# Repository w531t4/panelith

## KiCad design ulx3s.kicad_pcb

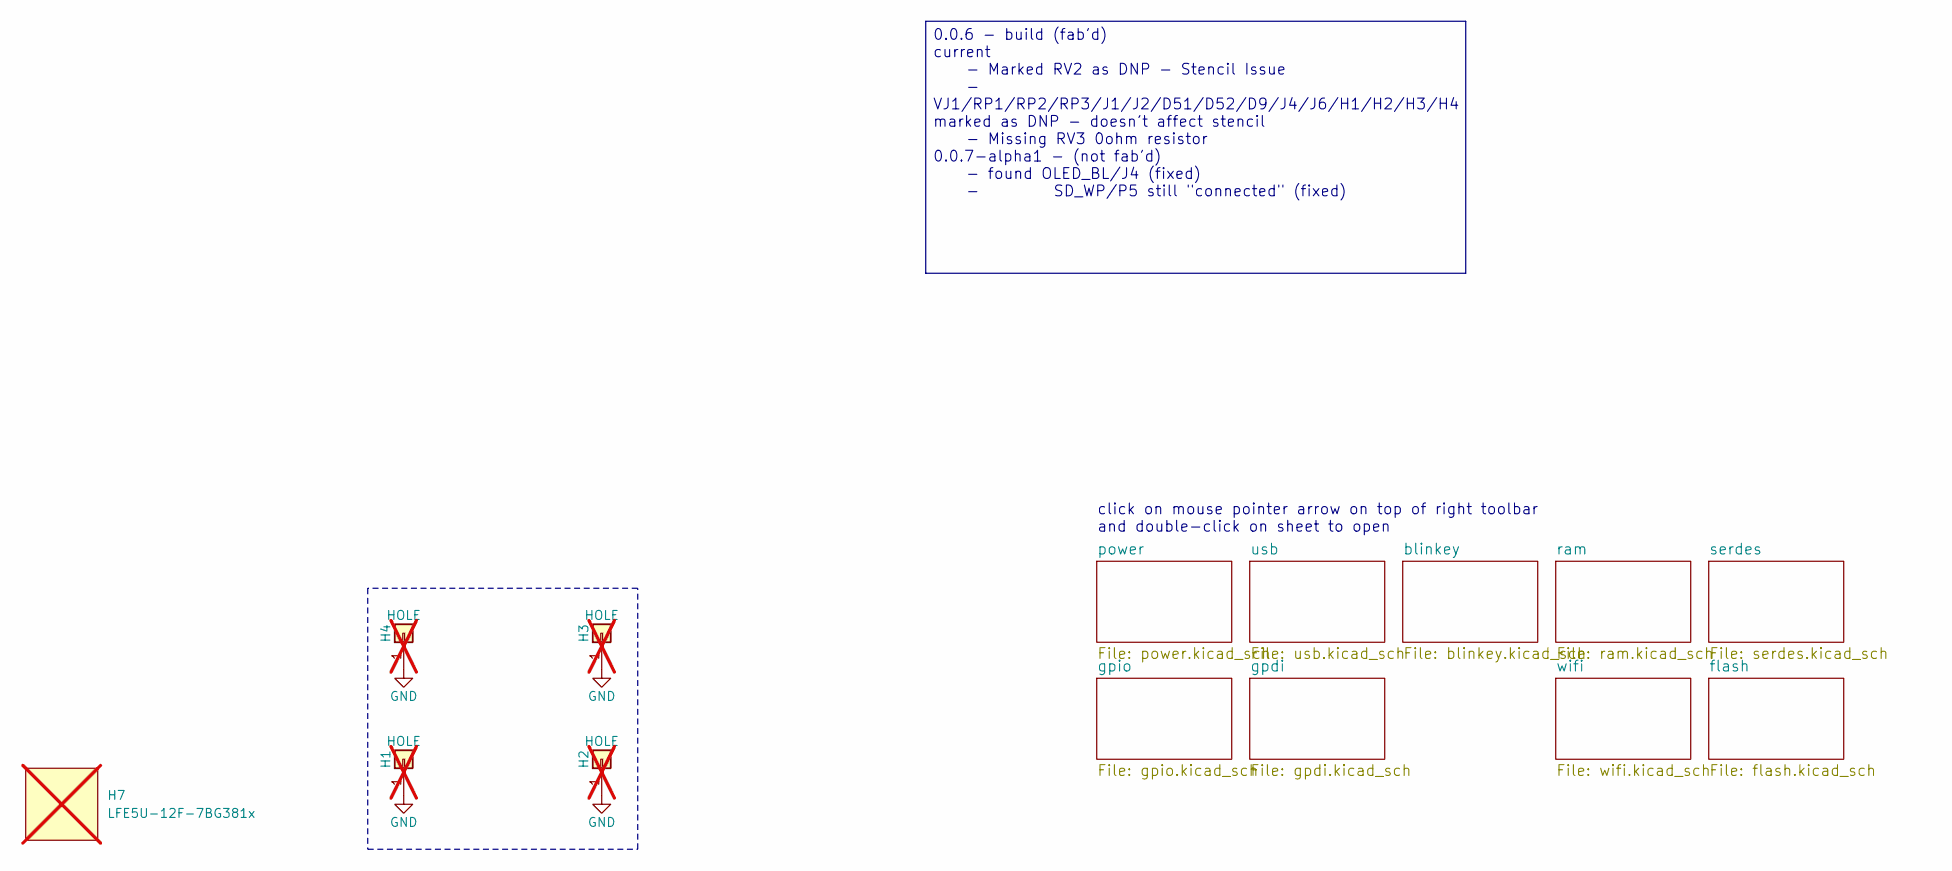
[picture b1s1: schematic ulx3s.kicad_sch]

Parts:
H1, H2, H3, H4: HOLE; MountingHole_3.2mm_M3_ISO14580_Pad; not fitted
H7: LFE5U-12F-7BG381x; Lattice_caBGA-381_17x17mm_Layout20x20_P0.8mm; MPN 842-LFE5U12F7BG381C; Digikey 220-2101-ND; not fitted

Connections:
unnamed: H1.1, H2.1, H3.1, H4.1

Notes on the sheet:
click on mouse pointer arrow on top of right toolbar and double-click on sheet to open
0.0.6 - build (fab'd) current - Marked RV2 as DNP - Stencil Issue - VJ1/RP1/RP2/RP3/J1/J2/D51/D52/D9/J4/J6/H1/H2/H3/H4 marked as DNP - doesn't affect stencil - Missing RV3 0ohm resistor 0.0.7-alpha1 - (not fab'd) - found OLED_BL/J4 (fixed) - SD_WP/P5 still "connected" (fixed)

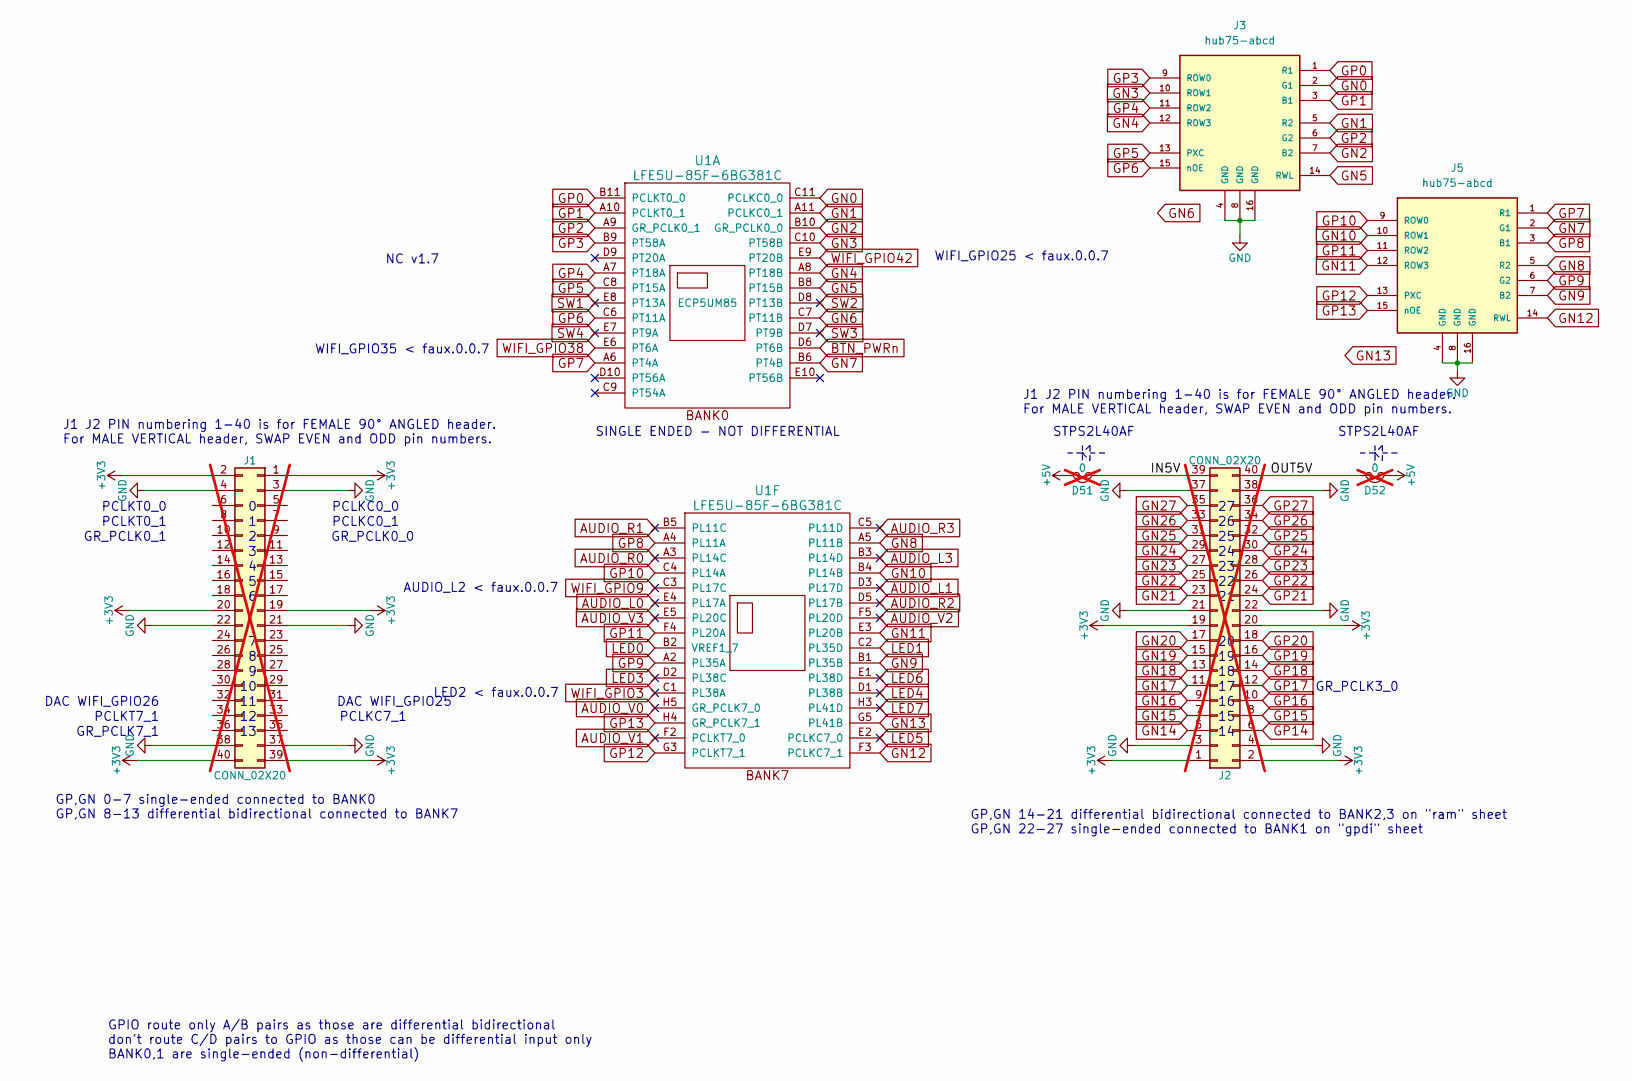
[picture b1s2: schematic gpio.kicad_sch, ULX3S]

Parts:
D51, D52: 0; D_SMA_Jumper_NC; not fitted
J1, J2: CONN_02X20; Socket_Strip_Angled_2x20; not fitted
J3, J5: hub75-abcd; SAMTEC-HTST-108-01-X-DV; MPN 200-HTST10801LDVP; Digikey SAM14030CT-ND
U1: LFE5U-85F-6BG381C; BGA-381_pitch0.8mm_dia0.4mm; MPN LFE5U-85F-6BG381C; LCSC C446029

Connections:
+5V: D51.1, D52.2; also elsewhere on the board
/gpio/IN5V: D51.2, J2.39
/gpio/OUT5V: D52.1, J2.40
AUDIO_L0: U1.E4 (PL17A)
AUDIO_L1: U1.D3 (PL17D)
AUDIO_L3: U1.B3 (PL14D)
AUDIO_R0: U1.A3 (PL14C)
AUDIO_R1: U1.B5 (PL11C)
AUDIO_R2: U1.D5 (PL17B)
AUDIO_R3: U1.C5 (PL11D)
AUDIO_V0: U1.H5 (GR_PCLK7_0)
AUDIO_V1: U1.F2 (PCLKT7_0)
AUDIO_V2: U1.F5 (PL20D)
AUDIO_V3: U1.E5 (PL20C)
BTN_PWRn: U1.D6 (PT6B); also elsewhere on the board
GN0: J3.2 (G1), U1.C11 (PCLKC0_0)
GN1: J3.5 (R2), U1.A11 (PCLKC0_1)
GN2: J3.7 (B2), U1.B10 (GR_PCLK0_0)
GN3: J3.10 (ROW1), U1.C10 (PT58B)
GN4: J3.12 (ROW3), U1.A8 (PT18B)
GN5: J3.14 (RWL), U1.B8 (PT15B)
GN6: U1.C7 (PT11B)
GN7: J5.2 (G1), U1.B6 (PT4B)
GN8: J5.5 (R2), U1.A5 (PL11B)
GN9: J5.7 (B2), U1.B1 (PL35B)
GN10: J5.10 (ROW1), U1.B4 (PL14B)
GN11: J5.12 (ROW3), U1.E3 (PL20B)
GN12: J5.14 (RWL), U1.F3 (PCLKC7_1); also elsewhere on the board
GN13: U1.G5 (PL41B); also elsewhere on the board
GND: J1.3, J1.4, J1.21, J1.22, J1.37, J1.38, J2.3, J2.4, J2.21, J2.22, J2.37, J2.38, J3.4 (GND), J3.8 (GND), J3.16 (GND), J5.4 (GND), J5.8 (GND), J5.16 (GND); also elsewhere on the board
GP0: J3.1 (R1), U1.B11 (PCLKT0_0)
GP1: J3.3 (B1), U1.A10 (PCLKT0_1)
GP2: J3.6 (G2), U1.A9 (GR_PCLK0_1)
GP3: J3.9 (ROW0), U1.B9 (PT58A)
GP4: J3.11 (ROW2), U1.A7 (PT18A)
GP5: J3.13 (PXC), U1.C8 (PT15A)
GP6: J3.15 (nOE), U1.C6 (PT11A)
GP7: J5.1 (R1), U1.A6 (PT4A)
GP8: J5.3 (B1), U1.A4 (PL11A)
GP9: J5.6 (G2), U1.A2 (PL35A)
GP10: J5.9 (ROW0), U1.C4 (PL14A)
GP11: J5.11 (ROW2), U1.F4 (PL20A)
GP12: J5.13 (PXC), U1.G3 (PCLKT7_1); also elsewhere on the board
GP13: J5.15 (nOE), U1.H4 (GR_PCLK7_1); also elsewhere on the board
LED0: U1.B2 (VREF1_7); also elsewhere on the board
LED1: U1.C2 (PL35D); also elsewhere on the board
LED3: U1.D2 (PL38C)
LED4: U1.D1 (PL38B)
LED5: U1.E2 (PCLKC7_0)
LED6: U1.E1 (PL38D)
LED7: U1.H3 (PL41D)
unnamed: J1.1, J1.2, J1.19, J1.20, J1.39, J1.40, J2.1, J2.2, J2.19, J2.20
SW1: U1.E8 (PT13A)
SW2: U1.D8 (PT13B)
SW3: U1.D7 (PT9B)
SW4: U1.E7 (PT9A)
WIFI_GPIO3: U1.C1 (PL38A); also elsewhere on the board
WIFI_GPIO9: U1.C3 (PL17C); also elsewhere on the board
WIFI_GPIO38: U1.E6 (PT6A); also elsewhere on the board
WIFI_GPIO42: U1.E9 (PT20B); also elsewhere on the board

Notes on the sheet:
GR_PCLK0_0
SINGLE ENDED - NOT DIFFERENTIAL
PCLKC0_1
LED2 < faux.0.0.7
J1 J2 PIN numbering 1-40 is for FEMALE 90° ANGLED header. For MALE VERTICAL header, SWAP EVEN and ODD pin numbers.
GPIO route only A/B pairs as those are differential bidirectional don't route C/D pairs to GPIO as those can be differential input only BANK0,1 are single-ended (non-differential)
WIFI_GPIO25 < faux.0.0.7
GP,GN 14-21 differential bidirectional connected to BANK2,3 on "ram" sheet GP,GN 22-27 single-ended connected to BANK1 on "gpdi" sheet
NC v1.7
AUDIO_L2 < faux.0.0.7
STPS2L40AF
DAC WIFI_GPIO26
GR_PCLK3_0
WIFI_GPIO35 < faux.0.0.7
PCLKT0_0
DAC WIFI_GPIO25
PCLKT7_1
PCLKT0_1
PCLKC7_1
GR_PCLK0_1
GR_PCLK7_1
PCLKC0_0
GP,GN 0-7 single-ended connected to BANK0 GP,GN 8-13 differential bidirectional connected to BANK7

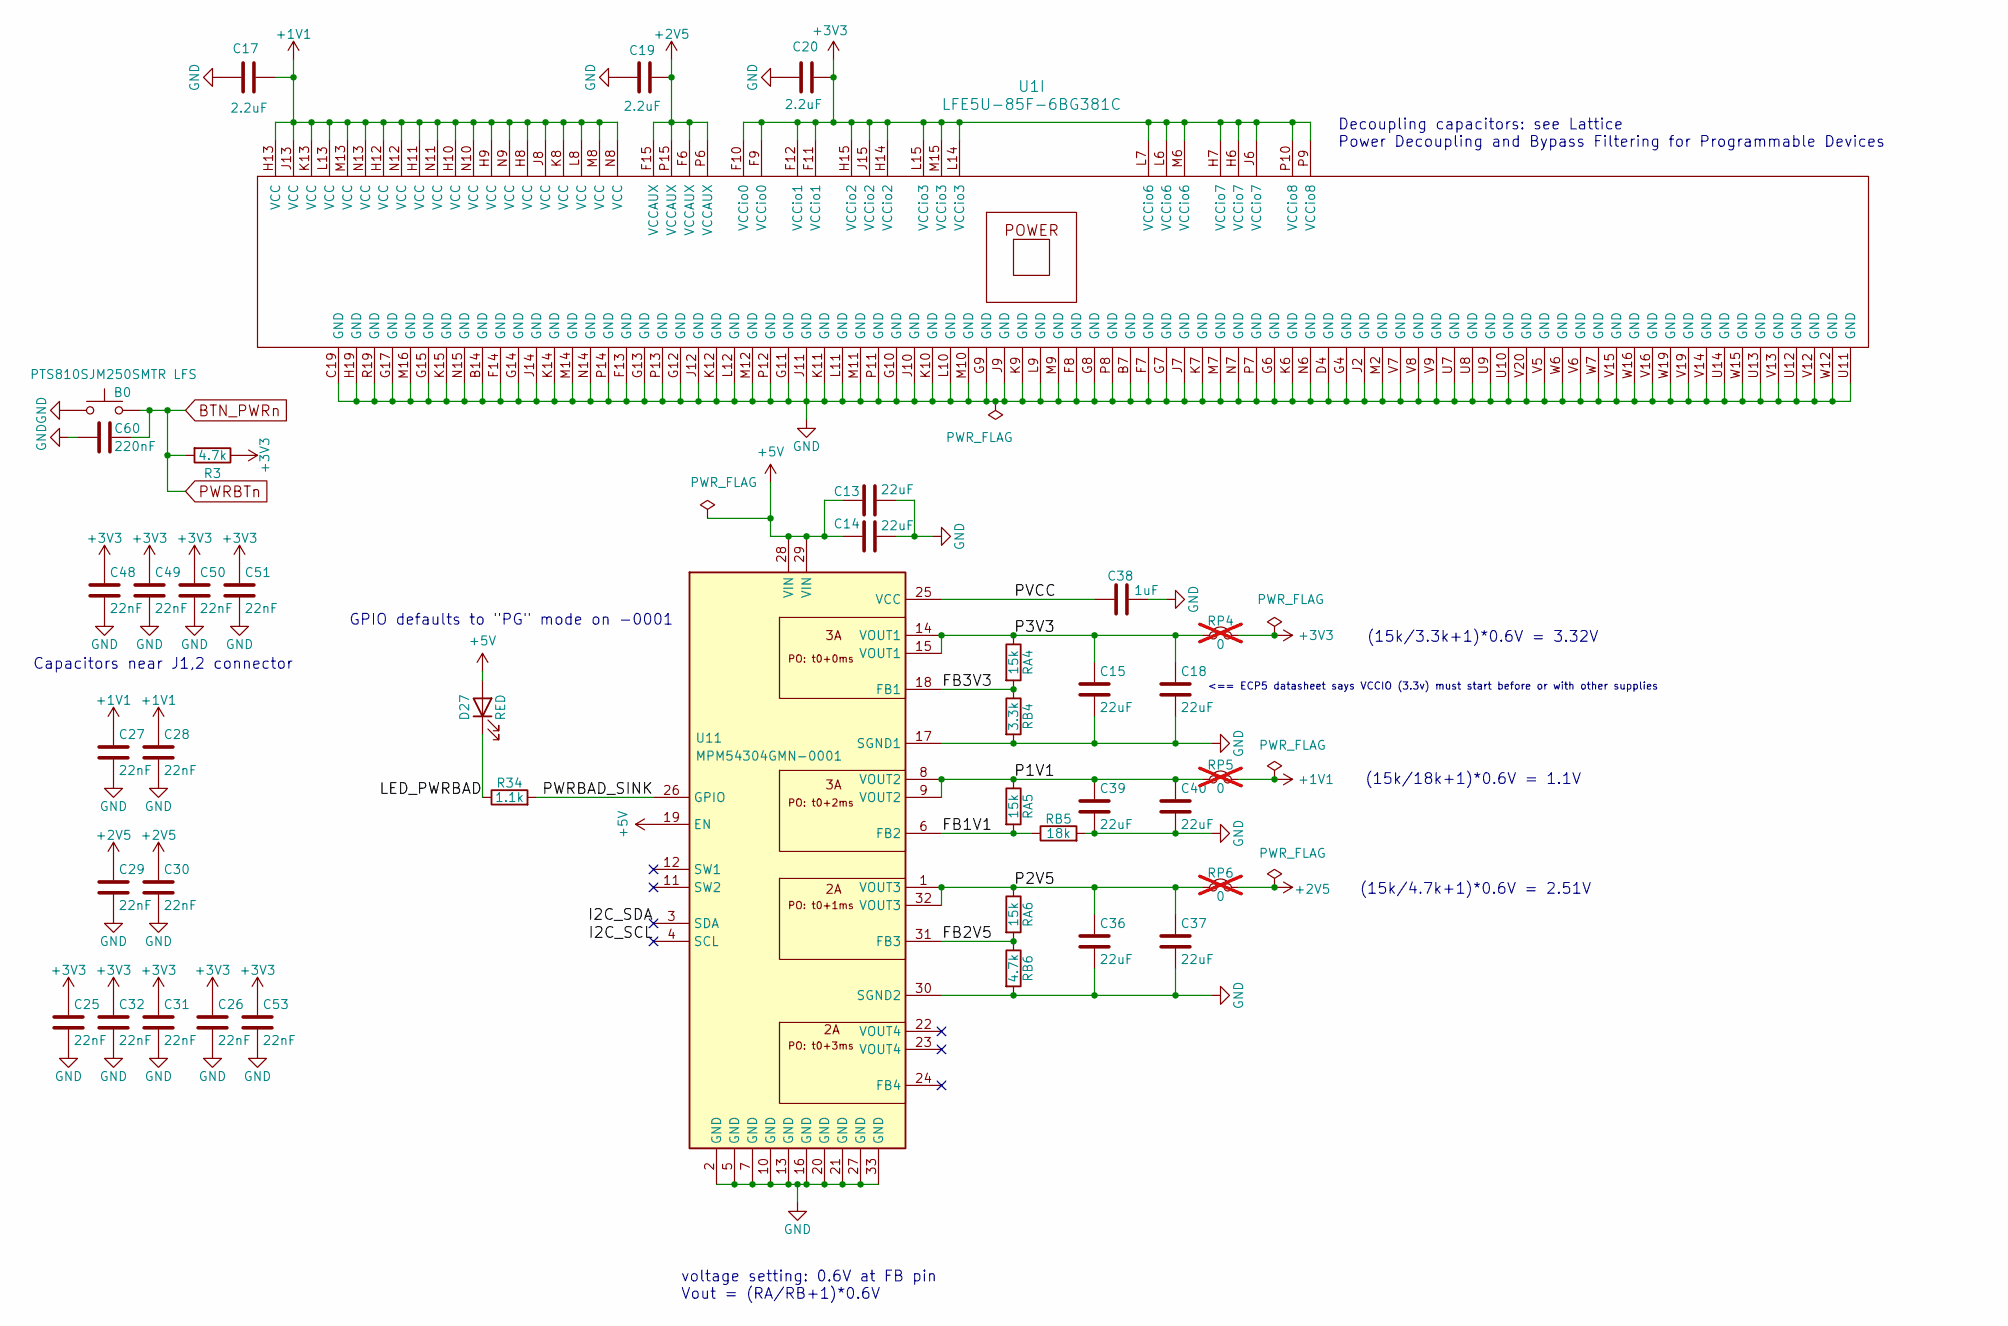
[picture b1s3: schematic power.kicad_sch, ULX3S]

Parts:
B0: PTS810SJM250SMTR LFS; PTS810_CNK; MPN 611-PTS810SJM250SMTR; Digikey CKN10502CT-ND
C13, C14: 22uF; C_0805_2012Metric; MPN 603-CC805MKX5R6BB226; Mouser 81-GRM21BR61A226ME1L
C15, C18, C36, C37, C39, C40: 22uF; C_0805_2012Metric; MPN 603-CC805MKX5R6BB226; Digikey 311-1900-1-ND
C17, C19, C20: 2.2uF; C_0805_2012Metric; MPN CC0805MRX5R6BB225; LCSC C87995
C25: 22nF; C_0603_1608Metric; MPN CC0603JRX7R8BB223; Mouser 603-CC603KRX7R7BB223
C26, C27, C28, C29, C30, C31, C32, C48, C49, C50, C51, C53: 22nF; C_0603_1608Metric; MPN CC0603JRX7R8BB223; LCSC C107137
C38: 1uF; C_0805_2012Metric; MPN 603-CC805KRX5R6BB105; Digikey 311-3423-1-ND
C60: 220nF; C_0603_1608Metric; MPN CC0603KRX7R8BB224; LCSC C326805
D27: RED; LED_0805_2012Metric; MPN LTST-C170KRKT; Mouser_URL www.mouser.com
R3: 4.7k; R_0603_1608Metric; MPN 603-RC0603FR-074K7L; LCSC C218056
R34: 1.1k; R_0603_1608Metric; MPN 13-AC0603FR-071K1LCT-ND; Digikey 13-AC0603FR-071K1LCT-ND
RA4, RA5, RA6: 15k; R_0603_1608Metric; MPN RC0603FR-0715KL; LCSC C217750
RB4: 3.3k; R_0603_1608Metric; MPN RT0603FRE073K3L; Mouser 603-RC0603FR-073K3L
RB5: 18k; R_0603_1608Metric; MPN RC0603FR-1018KL; Mouser 71-CRCW060318K0FKEAC
RB6: 4.7k; R_0603_1608Metric; MPN 603-RC0603FR-074K7L; LCSC C218056
RP4, RP5, RP6: 0; R_0805_2012Metric_Pad1.20x1.40mm_HandSolder; MPN 603-RC0805JR-070RL; Mouser_URL www.mouser.com; not fitted
U1: LFE5U-85F-6BG381C; BGA-381_pitch0.8mm_dia0.4mm; MPN LFE5U-85F-6BG381C; LCSC C446029
U11: MPM54304GMN-0001; MPM54304GMN0001; Manufacturer_Part_Number MPM54304GMN-0001; Mouser Part Number 946-MPM54304GMN-0001

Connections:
+1V1: C17.2, C27.1, C28.1, RP5.2, U1.H8 (VCC), U1.H9 (VCC), U1.H10 (VCC), U1.H11 (VCC), U1.H12 (VCC), U1.H13 (VCC), U1.J8 (VCC), U1.J13 (VCC), U1.K8 (VCC), U1.K13 (VCC), U1.L8 (VCC), U1.L13 (VCC), U1.M8 (VCC), U1.M13 (VCC), U1.N8 (VCC), U1.N9 (VCC), U1.N10 (VCC), U1.N11 (VCC), U1.N12 (VCC), U1.N13 (VCC)
+2V5: C19.1, C29.1, C30.1, RP6.2, U1.F6 (VCCAUX), U1.F15 (VCCAUX), U1.P6 (VCCAUX), U1.P15 (VCCAUX)
+3V3: C20.2, C25.1, C26.1, C31.1, C32.1, C48.1, C49.1, C50.1, C51.1, C53.1, R3.1, RP4.2, U1.F9 (VCCio0), U1.F10 (VCCio0), U1.F11 (VCCio1), U1.F12 (VCCio1), U1.H6 (VCCio7), U1.H7 (VCCio7), U1.H14 (VCCio2), U1.H15 (VCCio2), U1.J6 (VCCio7), U1.J15 (VCCio2), U1.L6 (VCCio6), U1.L7 (VCCio6), U1.L14 (VCCio3), U1.L15 (VCCio3), U1.M6 (VCCio6), U1.M15 (VCCio3), U1.P9 (VCCio8), U1.P10 (VCCio8); also elsewhere on the board
+5V: C13.1, C14.1, D27.2 (A), U11.19 (EN), U11.28 (VIN), U11.29 (VIN); also elsewhere on the board
/power/FB1V1: RA5.2, RB5.1, U11.6 (FB2)
/power/FB2V5: RA6.2, RB6.1, U11.31 (FB3)
/power/FB3V3: RA4.2, RB4.1, U11.18 (FB1)
/power/I2C_SCL: U11.4 (SCL)
/power/I2C_SDA: U11.3 (SDA)
/power/LED_PWRBAD: D27.1 (K), R34.1
/power/P1V1: C39.1, C40.1, RA5.1, RP5.1, U11.8 (VOUT2), U11.9 (VOUT2)
/power/P2V5: C36.1, C37.1, RA6.1, RP6.1, U11.1 (VOUT3), U11.32 (VOUT3)
/power/P3V3: C15.1, C18.1, RA4.1, RP4.1, U11.14 (VOUT1), U11.15 (VOUT1)
/power/PVCC: C38.1, U11.25 (VCC)
/power/PWRBAD_SINK: R34.2, U11.26 (GPIO)
BTN_PWRn: B0.1, C60.1, R3.2; also elsewhere on the board
GND: B0.2, C13.2, C14.2, C15.2, C17.1, C18.2, C19.2, C20.1, C25.2, C26.2, C27.2, C28.2, C29.2, C30.2, C31.2, C32.2, C36.2, C37.2, C38.2, C39.2, C40.2, C48.2, C49.2, C50.2, C51.2, C53.2, C60.2, RB4.2, RB5.2, RB6.2, U1.B7 (GND), U1.B14 (GND), U1.C19 (GND), U1.D4 (GND), U1.F7 (GND), U1.F8 (GND), U1.F13 (GND), U1.F14 (GND), U1.G4 (GND), U1.G6 (GND), U1.G7 (GND), U1.G8 (GND), U1.G9 (GND), U1.G10 (GND), U1.G11 (GND), U1.G12 (GND), U1.G13 (GND), U1.G14 (GND), U1.G15 (GND), U1.G17 (GND), U1.H19 (GND), U1.J2 (GND), U1.J7 (GND), U1.J9 (GND), U1.J10 (GND), U1.J11 (GND), U1.J12 (GND), U1.J14 (GND), U1.K6 (GND), U1.K7 (GND), U1.K9 (GND), U1.K10 (GND), U1.K11 (GND), U1.K12 (GND), U1.K14 (GND), U1.K15 (GND), U1.L9 (GND), U1.L10 (GND), U1.L11 (GND), U1.L12 (GND), U1.M2 (GND), U1.M7 (GND), U1.M9 (GND), U1.M10 (GND), U1.M11 (GND), U1.M12 (GND), U1.M14 (GND), U1.M16 (GND), U1.N6 (GND), U1.N7 (GND), U1.N14 (GND), U1.N15 (GND), U1.P7 (GND), U1.P8 (GND), U1.P11 (GND), U1.P12 (GND), U1.P13 (GND), U1.P14 (GND), U1.R19 (GND), U1.U7 (GND), U1.U8 (GND), U1.U9 (GND), U1.U10 (GND), U1.U11 (GND), U1.U12 (GND), U1.U13 (GND), U1.U14 (GND), U1.V5 (GND), U1.V6 (GND), U1.V7 (GND), U1.V8 (GND), U1.V9 (GND), U1.V12 (GND), U1.V13 (GND), U1.V14 (GND), U1.V15 (GND), U1.V16 (GND), U1.V19 (GND), U1.V20 (GND), U1.W6 (GND), U1.W7 (GND), U1.W12 (GND), U1.W15 (GND), U1.W16 (GND), U1.W19 (GND), U11.2 (GND), U11.5 (GND), U11.7 (GND), U11.10 (GND), U11.13 (GND), U11.16 (GND), U11.17 (SGND1), U11.20 (GND), U11.21 (GND), U11.27 (GND), U11.30 (SGND2), U11.33 (GND); also elsewhere on the board

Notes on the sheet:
GPIO defaults to "PG" mode on -0001
(15k/4.7k+1)*0.6V = 2.51V
<== ECP5 datasheet says VCCIO (3.3v) must start before or with other supplies
(15k/18k+1)*0.6V = 1.1V
Decoupling capacitors: see Lattice Power Decoupling and Bypass Filtering for Programmable Devices
(15k/3.3k+1)*0.6V = 3.32V
Capacitors near J1,2 connector
voltage setting: 0.6V at FB pin Vout = (RA/RB+1)*0.6V

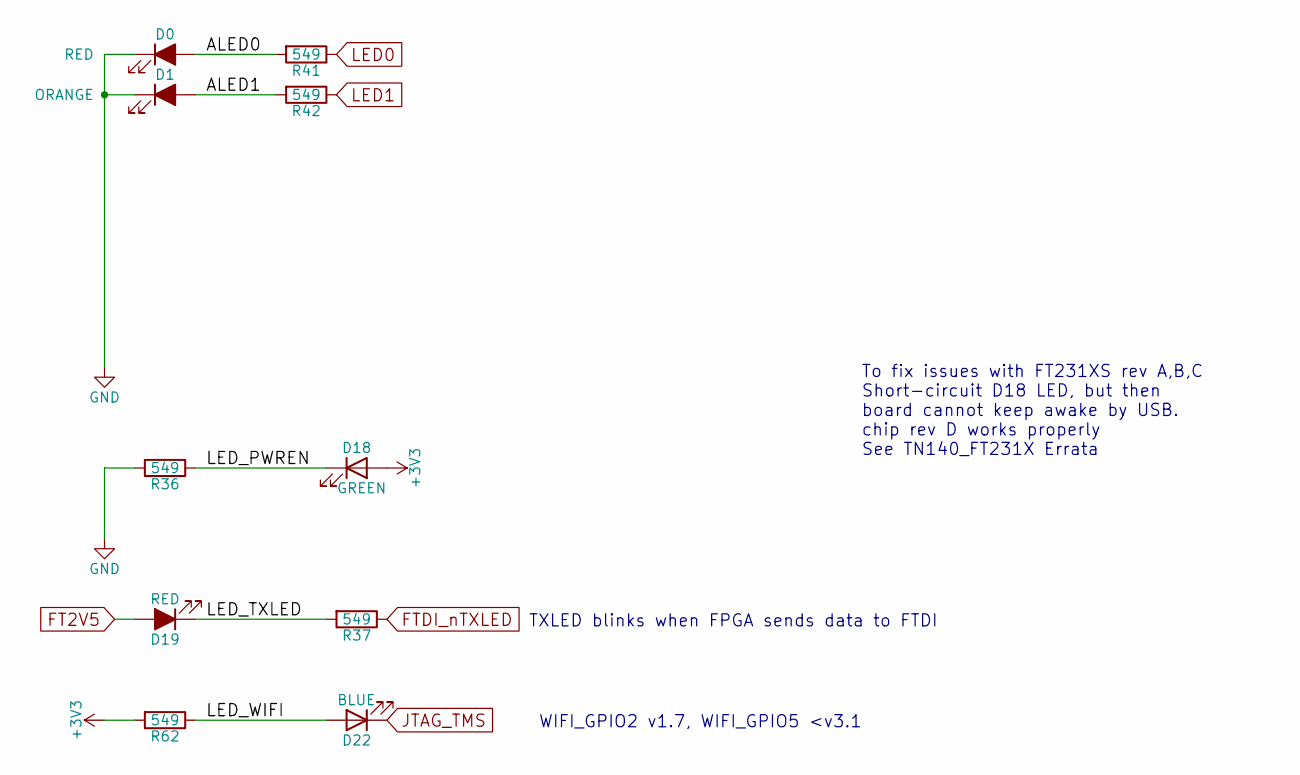
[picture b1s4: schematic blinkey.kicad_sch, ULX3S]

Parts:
D0: RED; LED_0805_2012Metric; MPN LTST-C170KRKT; Mouser 859-LTST-C170KRKT
D1: ORANGE; LED_0805_2012Metric; MPN LTST-C170KFKT; Mouser 859-LTST-C170KFKT
D18: GREEN; LED_0805_2012Metric; MPN LTST-C170TGKT; Mouser 859-LTST-C170TGKT
D19: RED; LED_0805_2012Metric; MPN LTST-C170KRKT; Mouser_URL www.mouser.com
D22: BLUE; LED_0805_2012Metric; MPN LTST-C170TBKT; Mouser 859-LTST-C170TBKT
R36, R37, R41, R42, R62: 549; R_0603_1608Metric; MPN 13-AC0603FR-07549RLCT-ND; Digikey 13-AC0603FR-07549RLCT-ND

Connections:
+3V3: D18.2 (A), R62.2; also elsewhere on the board
/blinkey/ALED0: D0.2 (A), R41.2
/blinkey/ALED1: D1.2 (A), R42.2
/blinkey/LED_PWREN: D18.1 (K), R36.1
/blinkey/LED_TXLED: D19.1 (K), R37.2
/blinkey/LED_WIFI: D22.2 (A), R62.1
FT2V5: D19.2 (A); also elsewhere on the board
FTDI_nTXLED: R37.1; also elsewhere on the board
GND: D0.1 (K), D1.1 (K), R36.2; also elsewhere on the board
JTAG_TMS: D22.1 (K); also elsewhere on the board
LED0: R41.1; also elsewhere on the board
LED1: R42.1; also elsewhere on the board

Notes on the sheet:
To fix issues with FT231XS rev A,B,C Short-circuit D18 LED, but then board cannot keep awake by USB. chip rev D works properly See TN140_FT231X Errata
TXLED blinks when FPGA sends data to FTDI
WIFI_GPIO2 v1.7, WIFI_GPIO5 <v3.1

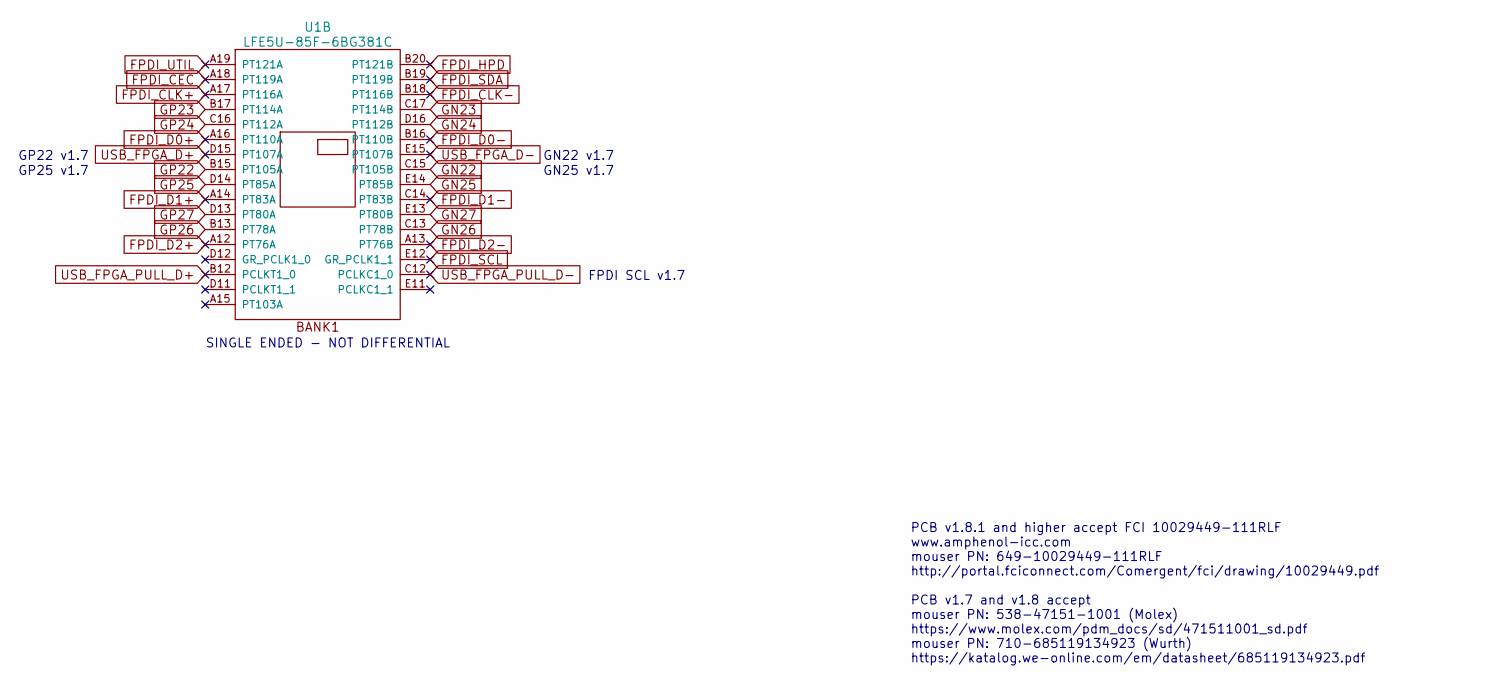
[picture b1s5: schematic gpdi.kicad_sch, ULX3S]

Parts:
U1: LFE5U-85F-6BG381C; BGA-381_pitch0.8mm_dia0.4mm; MPN LFE5U-85F-6BG381C; Mouser_URL www.mouser.com

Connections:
FPDI_CEC: U1.A18 (PT119A)
FPDI_CLK+: U1.A17 (PT116A)
FPDI_CLK-: U1.B18 (PT116B)
FPDI_D0+: U1.A16 (PT110A)
FPDI_D0-: U1.B16 (PT110B)
FPDI_D1+: U1.A14 (PT83A)
FPDI_D1-: U1.C14 (PT83B)
FPDI_D2+: U1.A12 (PT76A)
FPDI_D2-: U1.A13 (PT76B)
FPDI_HPD: U1.B20 (PT121B)
FPDI_SCL: U1.E12 (GR_PCLK1_1)
FPDI_SDA: U1.B19 (PT119B)
FPDI_UTIL: U1.A19 (PT121A)
GN22: U1.C15 (PT105B)
GN23: U1.C17 (PT114B)
GN24: U1.D16 (PT112B)
GN25: U1.E14 (PT85B)
GN26: U1.C13 (PT78B)
GN27: U1.E13 (PT80B)
GP22: U1.B15 (PT105A)
GP23: U1.B17 (PT114A)
GP24: U1.C16 (PT112A)
GP25: U1.D14 (PT85A)
GP26: U1.B13 (PT78A)
GP27: U1.D13 (PT80A)
USB_FPGA_D+: U1.D15 (PT107A); also elsewhere on the board
USB_FPGA_D-: U1.E15 (PT107B); also elsewhere on the board
USB_FPGA_PULL_D+: U1.B12 (PCLKT1_0)
USB_FPGA_PULL_D-: U1.C12 (PCLKC1_0)

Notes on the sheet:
PCB v1.8.1 and higher accept FCI 10029449-111RLF www.amphenol-icc.com mouser PN: 649-10029449-111RLF http://portal.fciconnect.com/Comergent/fci/drawing/10029449.pdf PCB v1.7 and v1.8 accept mouser PN: 538-47151-1001 (Molex) https://www.molex.com/pdm_docs/sd/471511001_sd.pdf mouser PN: 710-685119134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
GN22 v1.7
GN25 v1.7
GP25 v1.7
FPDI SCL v1.7
SINGLE ENDED - NOT DIFFERENTIAL
GP22 v1.7

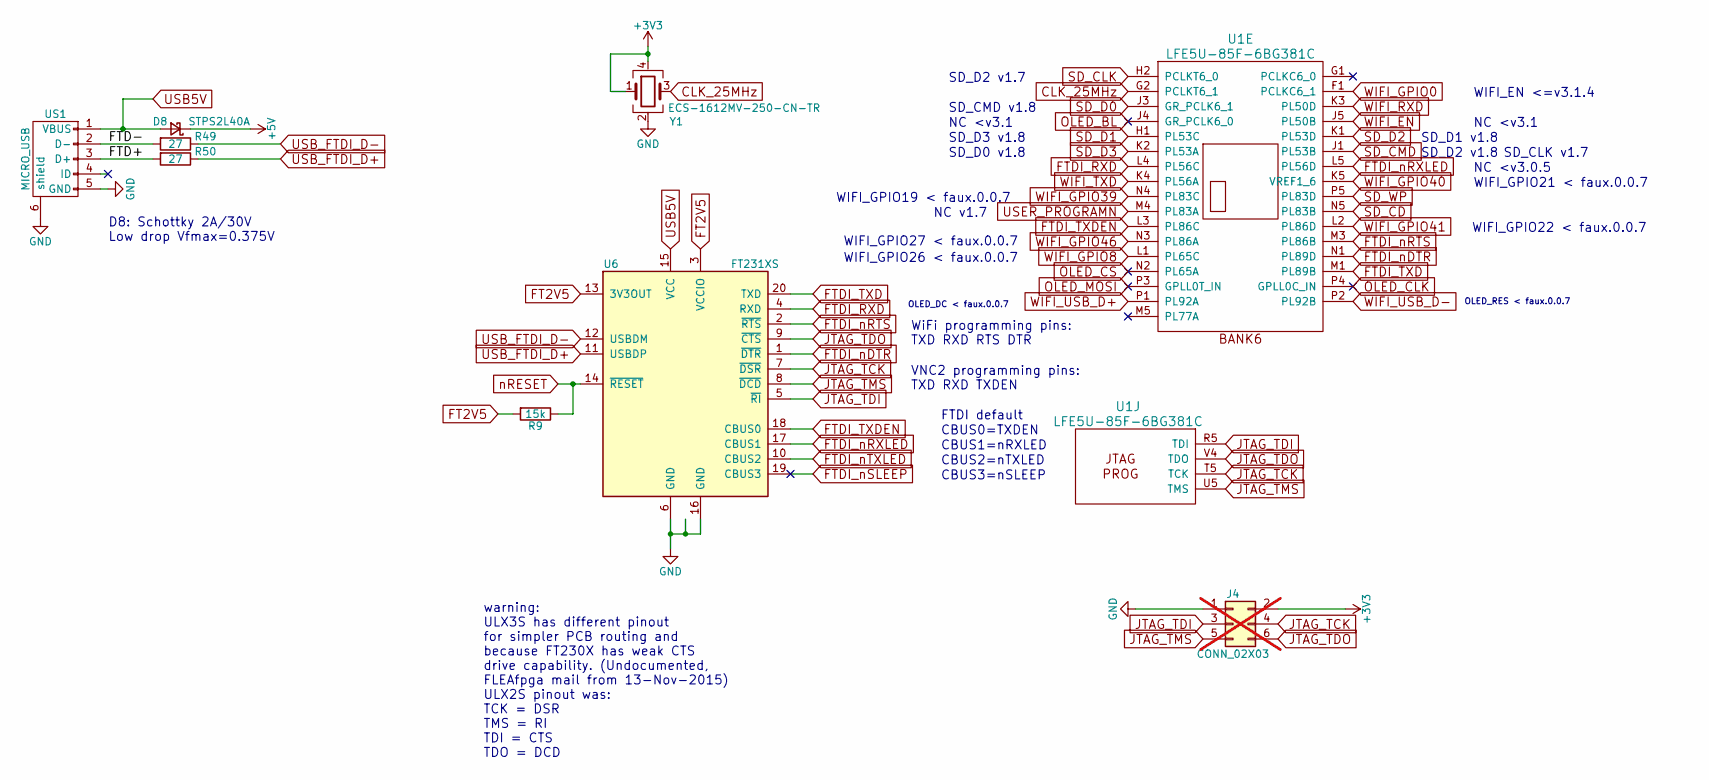
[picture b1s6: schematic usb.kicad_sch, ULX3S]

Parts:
D8: STPS2L40A; D_SMA; MPN 511-STPS2L30A; Mouser 511-STPS2L40AF
J4: CONN_02X03; PinSocket_2x03_P2.54mm_Vertical; not fitted
R9: 15k; R_0603_1608Metric; MPN RC0603FR-0715KL; Mouser 603-AC0603FR-1015KL
R49: 27; R_0603_1608Metric; MPN AC0603JR-0727RL; Mouser 603-AC0603JR-0727RL
R50: 27; R_0603_1608Metric; MPN AC0603JR-0727RL; LCSC C325726
U1: LFE5U-85F-6BG381C; BGA-381_pitch0.8mm_dia0.4mm; MPN LFE5U-85F-6BG381C; LCSC C446029
U6: FT231XS; FT231X-SSOP-20_4.4x6.5mm_Pitch0.65mm; MPN 895-FT231XS-U; Mouser 895-FT231XQ-R
US1: MICRO_USB; USB-MICRO-B-FCI-10118192-0001LF; MPN 10118192-0001LF; Mouser 649-10118192-0001LF
Y1: ECS-1612MV-250-CN-TR; OSC_ECS-1612MV-250-CN-TR-4; MPN 520-1612MV-250-CNT; Digikey XC2830CT-ND

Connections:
+3V3: J4.2, Y1.1, Y1.4 (VDD); also elsewhere on the board
+5V: D8.1 (K); also elsewhere on the board
/usb/FTD+: R50.2, US1.3 (D+)
/usb/FTD-: R49.2, US1.2 (D-)
CLK_25MHz: U1.G2 (PCLKT6_1), Y1.3
FT2V5: R9.2, U6.3 (VCCIO), U6.13 (3V3OUT); also elsewhere on the board
FTDI_RXD: U1.L4 (PL56C), U6.4 (RXD)
FTDI_TXD: U1.M1 (PL89B), U6.20 (TXD)
FTDI_TXDEN: U1.L3 (PL86C), U6.18 (CBUS0)
FTDI_nDTR: U1.N1 (PL89D), U6.1 (~DTR)
FTDI_nRTS: U1.M3 (PL86B), U6.2 (~RTS)
FTDI_nRXLED: U1.L5 (PL56D), U6.17 (CBUS1)
FTDI_nSLEEP: U6.19 (CBUS3)
FTDI_nTXLED: U6.10 (CBUS2); also elsewhere on the board
GND: J4.1, U6.6 (GND), U6.16 (GND), US1.5 (GND), US1.6 (shield), Y1.2 (GND); also elsewhere on the board
JTAG_TCK: J4.4, U1.T5 (TCK), U6.7 (~DSR); also elsewhere on the board
JTAG_TDI: J4.3, U1.R5 (TDI), U6.5 (~RI); also elsewhere on the board
JTAG_TDO: J4.6, U1.V4 (TDO), U6.9 (~CTS); also elsewhere on the board
JTAG_TMS: J4.5, U1.U5 (TMS), U6.8 (~DCD); also elsewhere on the board
OLED_BL: U1.J4 (GR_PCLK6_0)
OLED_CLK: U1.P4 (GPLL0C_IN)
OLED_CS: U1.N2 (PL65A)
OLED_MOSI: U1.P3 (GPLL0T_IN)
SD_CD: U1.N5 (PL83B)
SD_CLK: U1.H2 (PCLKT6_0); also elsewhere on the board
SD_CMD: U1.J1 (PL53B); also elsewhere on the board
SD_D0: U1.J3 (GR_PCLK6_1); also elsewhere on the board
SD_D1: U1.H1 (PL53C); also elsewhere on the board
SD_D2: U1.K1 (PL53D); also elsewhere on the board
SD_D3: U1.K2 (PL53A); also elsewhere on the board
SD_WP: U1.P5 (PL83D)
USB5V: D8.2 (A), U6.15 (VCC), US1.1 (VBUS)
USB_FTDI_D+: R50.1, U6.11 (USBDP)
USB_FTDI_D-: R49.1, U6.12 (USBDM)
USER_PROGRAMN: U1.M4 (PL83A); also elsewhere on the board
WIFI_EN: U1.J5 (PL50B); also elsewhere on the board
WIFI_GPIO0: U1.F1 (PCLKC6_1); also elsewhere on the board
WIFI_GPIO8: U1.L1 (PL65C); also elsewhere on the board
WIFI_GPIO39: U1.N4 (PL83C); also elsewhere on the board
WIFI_GPIO40: U1.K5 (VREF1_6); also elsewhere on the board
WIFI_GPIO41: U1.L2 (PL86D); also elsewhere on the board
WIFI_GPIO46: U1.N3 (PL86A); also elsewhere on the board
WIFI_RXD: U1.K3 (PL50D); also elsewhere on the board
WIFI_TXD: U1.K4 (PL56A); also elsewhere on the board
WIFI_USB_D+: U1.P1 (PL92A); also elsewhere on the board
WIFI_USB_D-: U1.P2 (PL92B); also elsewhere on the board
nRESET: R9.1, U6.14 (~RESET)

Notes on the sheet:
WIFI_EN <=v3.1.4
CBUS3=nSLEEP
SD_CLK v1.7
OLED_DC < faux.0.0.7
SD_D0 v1.8
CBUS1=nRXLED
WIFI_GPIO22 < faux.0.0.7
SD_D2 v1.7
NC <v3.1
FTDI default
WIFI_GPIO27 < faux.0.0.7
SD_CMD v1.8
warning: ULX3S has different pinout for simpler PCB routing and because FT230X has weak CTS drive capability. (Undocumented, FLEAfpga mail from 13-Nov-2015) ULX2S pinout was: TCK = DSR TMS = RI TDI = CTS TDO = DCD
OLED_RES < faux.0.0.7
CBUS2=nTXLED
CBUS0=TXDEN
NC v1.7
WiFi programming pins: TXD RXD RTS DTR
NC <v3.0.5
VNC2 programming pins: TXD RXD TXDEN
WIFI_GPIO19 < faux.0.0.7
WIFI_GPIO21 < faux.0.0.7
WIFI_GPIO26 < faux.0.0.7
D8: Schottky 2A/30V Low drop Vfmax=0.375V
SD_D1 v1.8
SD_D3 v1.8
SD_D2 v1.8

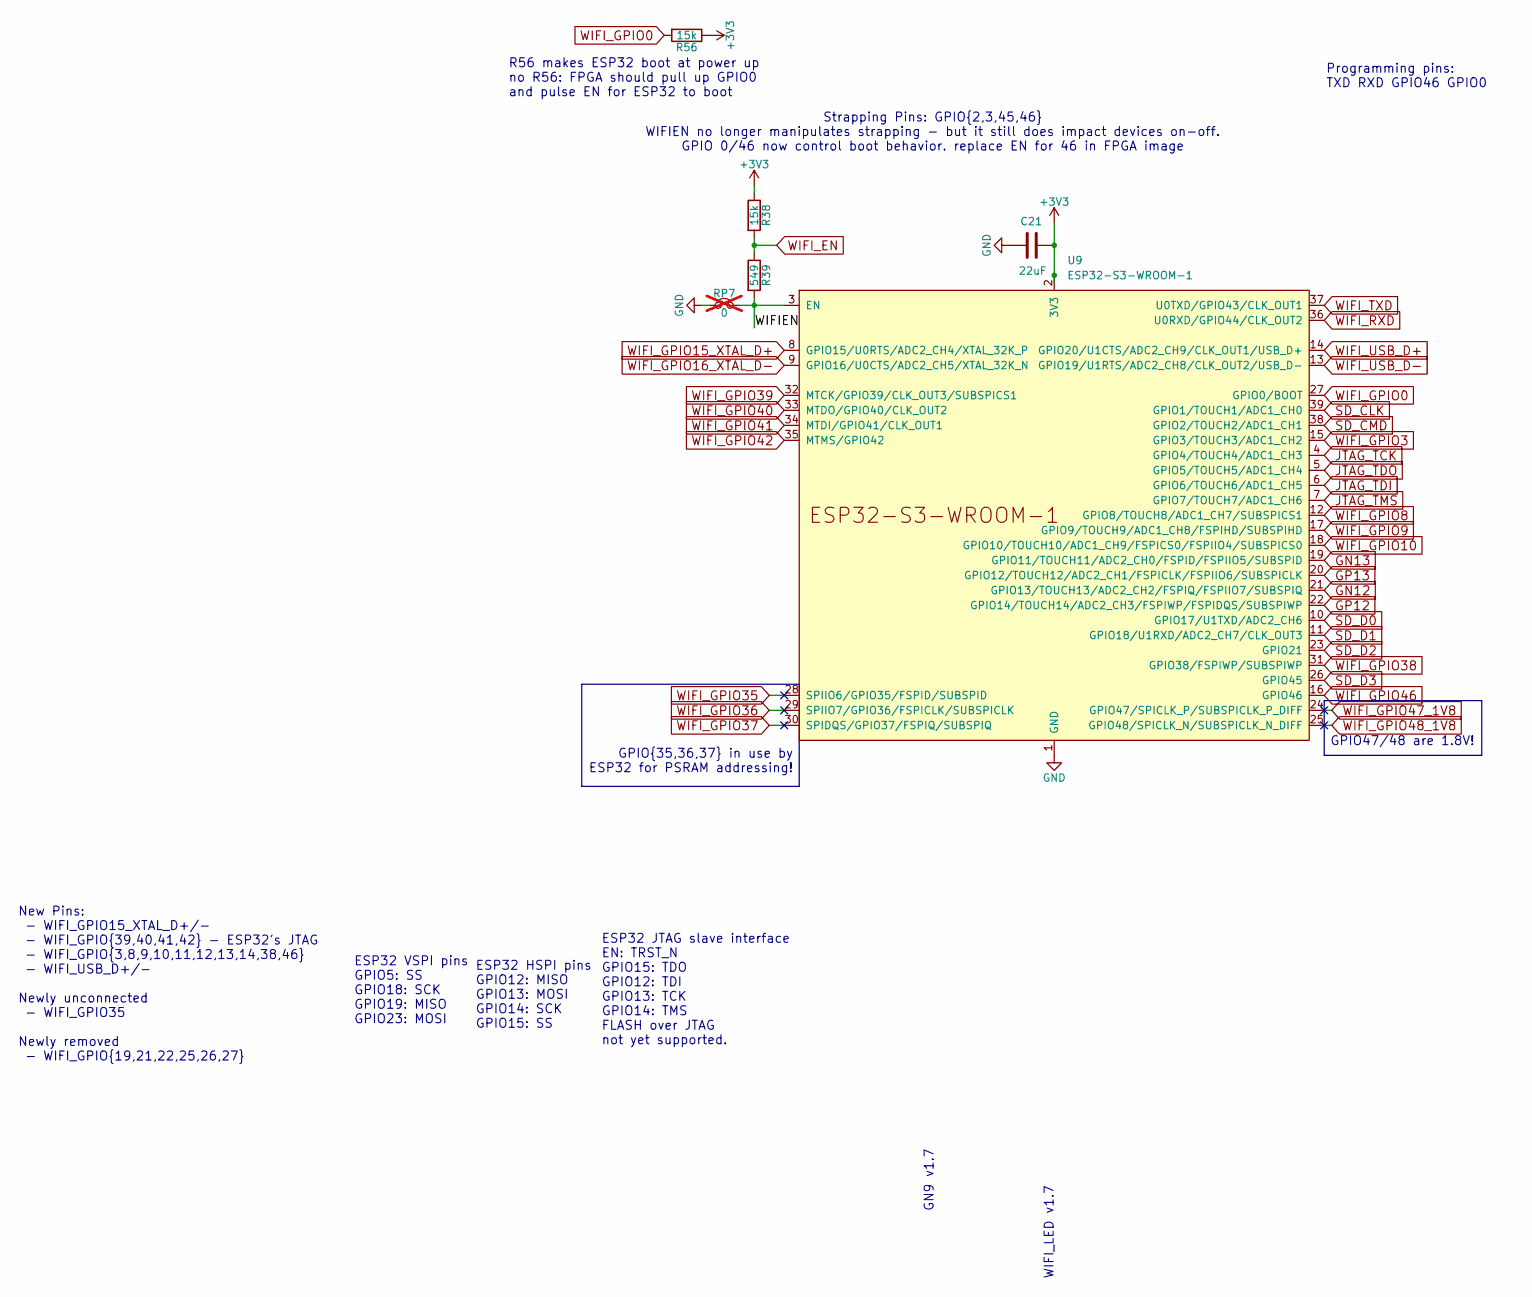
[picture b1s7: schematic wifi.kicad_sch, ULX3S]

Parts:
C21: 22uF; C_0805_2012Metric; MPN 603-CC805MKX5R6BB226; Digikey 311-1900-1-ND
R38, R56: 15k; R_0603_1608Metric; MPN RC0603FR-0715KL; LCSC C217750
R39: 549; R_0603_1608Metric; MPN 13-AC0603FR-07549RLCT-ND; Digikey 13-AC0603FR-07549RLCT-ND
RP7: 0; R_0805_2012Metric_Pad1.20x1.40mm_HandSolder; MPN 603-RC0805JR-070RL; Mouser_URL www.mouser.com; not fitted
U9: ESP32-S3-WROOM-1; MPN 356-ESP32S3WRM1N16R8; Digikey 5407-ESP32-S3-WROOM-1-N16R8CT-ND

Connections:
+3V3: C21.1, R38.1, R56.1, U9.2 (3V3); also elsewhere on the board
/wifi/WIFIEN: R39.2, RP7.2, U9.3 (EN)
GN12: U9.21 (GPIO13/TOUCH13/ADC2_CH2/FSPIQ/FSPIIO7/S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); also elsewhere on the board
GN13: U9.19 (GPIO11/TOUCH11/ADC2_CH0/FSPID/FSPIIO5/S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); also elsewhere on the board
GND: C21.2, RP7.1, U9.1 (GND), U9.40 (GND), U9.41 (GND); also elsewhere on the board
GP12: U9.22 (GPIO14/TOUCH14/ADC2_CH3/FSPIWP/FSPIDQS/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); also elsewhere on the board
GP13: U9.20 (GPIO12/TOUCH12/ADC2_CH1/FSPICLK/FSPIIO6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); also elsewhere on the board
JTAG_TCK: U9.4 (GPIO4/TOUCH4/ADC1_CH3); also elsewhere on the board
JTAG_TDI: U9.6 (GPIO6/TOUCH6/ADC1_CH5); also elsewhere on the board
JTAG_TDO: U9.5 (GPIO5/TOUCH5/ADC1_CH4); also elsewhere on the board
JTAG_TMS: U9.7 (GPIO7/TOUCH7/ADC1_CH6); also elsewhere on the board
SD_CLK: U9.39 (GPIO1/TOUCH1/ADC1_CH0); also elsewhere on the board
SD_CMD: U9.38 (GPIO2/TOUCH2/ADC1_CH1); also elsewhere on the board
SD_D0: U9.10 (GPIO17/U1TXD/ADC2_CH6); also elsewhere on the board
SD_D1: U9.11 (GPIO18/U1RXD/ADC2_CH7/CLK_OUT3); also elsewhere on the board
SD_D2: U9.23 (GPIO21); also elsewhere on the board
SD_D3: U9.26 (GPIO45); also elsewhere on the board
WIFI_EN: R38.2, R39.1; also elsewhere on the board
WIFI_GPIO0: R56.2, U9.27 (GPIO0/BOOT); also elsewhere on the board
WIFI_GPIO3: U9.15 (GPIO3/TOUCH3/ADC1_CH2); also elsewhere on the board
WIFI_GPIO8: U9.12 (GPIO8/TOUCH8/ADC1_CH7/SUBSPICS1); also elsewhere on the board
WIFI_GPIO9: U9.17 (GPIO9/TOUCH9/ADC1_CH8/FSPIHD/SUBSPIHD); also elsewhere on the board
WIFI_GPIO10: U9.18 (GPIO10/TOUCH10/ADC1_CH9/FSPICS0/FSPIIO4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)
WIFI_GPIO15_XTAL_D+: U9.8 (GPIO15/U0RTS/ADC2_CH4/XTAL_32K_P)
WIFI_GPIO16_XTAL_D-: U9.9 (GPIO16/U0CTS/ADC2_CH5/XTAL_32K_N)
WIFI_GPIO35: U9.28 (SPIIO6/GPIO35/FSPID/SUBSPID)
WIFI_GPIO36: U9.29 (SPIIO7/GPIO36/FSPICLK/SUBSPICLK)
WIFI_GPIO37: U9.30 (SPIDQS/GPIO37/FSPIQ/SUBSPIQ)
WIFI_GPIO38: U9.31 (GPIO38/FSPIWP/SUBSPIWP); also elsewhere on the board
WIFI_GPIO39: U9.32 (MTCK/GPIO39/CLK_OUT3/SUBSPICS1); also elsewhere on the board
WIFI_GPIO40: U9.33 (MTDO/GPIO40/CLK_OUT2); also elsewhere on the board
WIFI_GPIO41: U9.34 (MTDI/GPIO41/CLK_OUT1); also elsewhere on the board
WIFI_GPIO42: U9.35 (MTMS/GPIO42); also elsewhere on the board
WIFI_GPIO46: U9.16 (GPIO46); also elsewhere on the board
WIFI_GPIO47_1V8: U9.24 (GPIO47/SPICLK_P/SUBSPICLK_P_DIFF)
WIFI_GPIO48_1V8: U9.25 (GPIO48/SPICLK_N/SUBSPICLK_N_DIFF)
WIFI_RXD: U9.36 (U0RXD/GPIO44/CLK_OUT2); also elsewhere on the board
WIFI_TXD: U9.37 (U0TXD/GPIO43/CLK_OUT1); also elsewhere on the board
WIFI_USB_D+: U9.14 (GPIO20/U1CTS/ADC2_CH9/CLK_OUT1/USB_D+); also elsewhere on the board
WIFI_USB_D-: U9.13 (GPIO19/U1RTS/ADC2_CH8/CLK_OUT2/USB_D-); also elsewhere on the board

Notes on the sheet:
WIFI_LED v1.7
ESP32 VSPI pins GPIO5: SS GPIO18: SCK GPIO19: MISO GPIO23: MOSI
GN9 v1.7
Programming pins: TXD RXD GPIO46 GPIO0
New Pins: - WIFI_GPIO15_XTAL_D+/- - WIFI_GPIO{39,40,41,42} - ESP32's JTAG - WIFI_GPIO{3,8,9,10,11,12,13,14,38,46} - WIFI_USB_D+/- Newly unconnected - WIFI_GPIO35 Newly removed - WIFI_GPIO{19,21,22,25,26,27}
ESP32 HSPI pins GPIO12: MISO GPIO13: MOSI GPIO14: SCK GPIO15: SS
ESP32 JTAG slave interface EN: TRST_N GPIO15: TDO GPIO12: TDI GPIO13: TCK GPIO14: TMS FLASH over JTAG not yet supported.
Strapping Pins: GPIO{2,3,45,46} WIFIEN no longer manipulates strapping - but it still does impact devices on-off. GPIO 0/46 now control boot behavior. replace EN for 46 in FPGA image
R56 makes ESP32 boot at power up no R56: FPGA should pull up GPIO0 and pulse EN for ESP32 to boot
GPIO47/48 are 1.8V!
GPIO{35,36,37} in use by ESP32 for PSRAM addressing!
